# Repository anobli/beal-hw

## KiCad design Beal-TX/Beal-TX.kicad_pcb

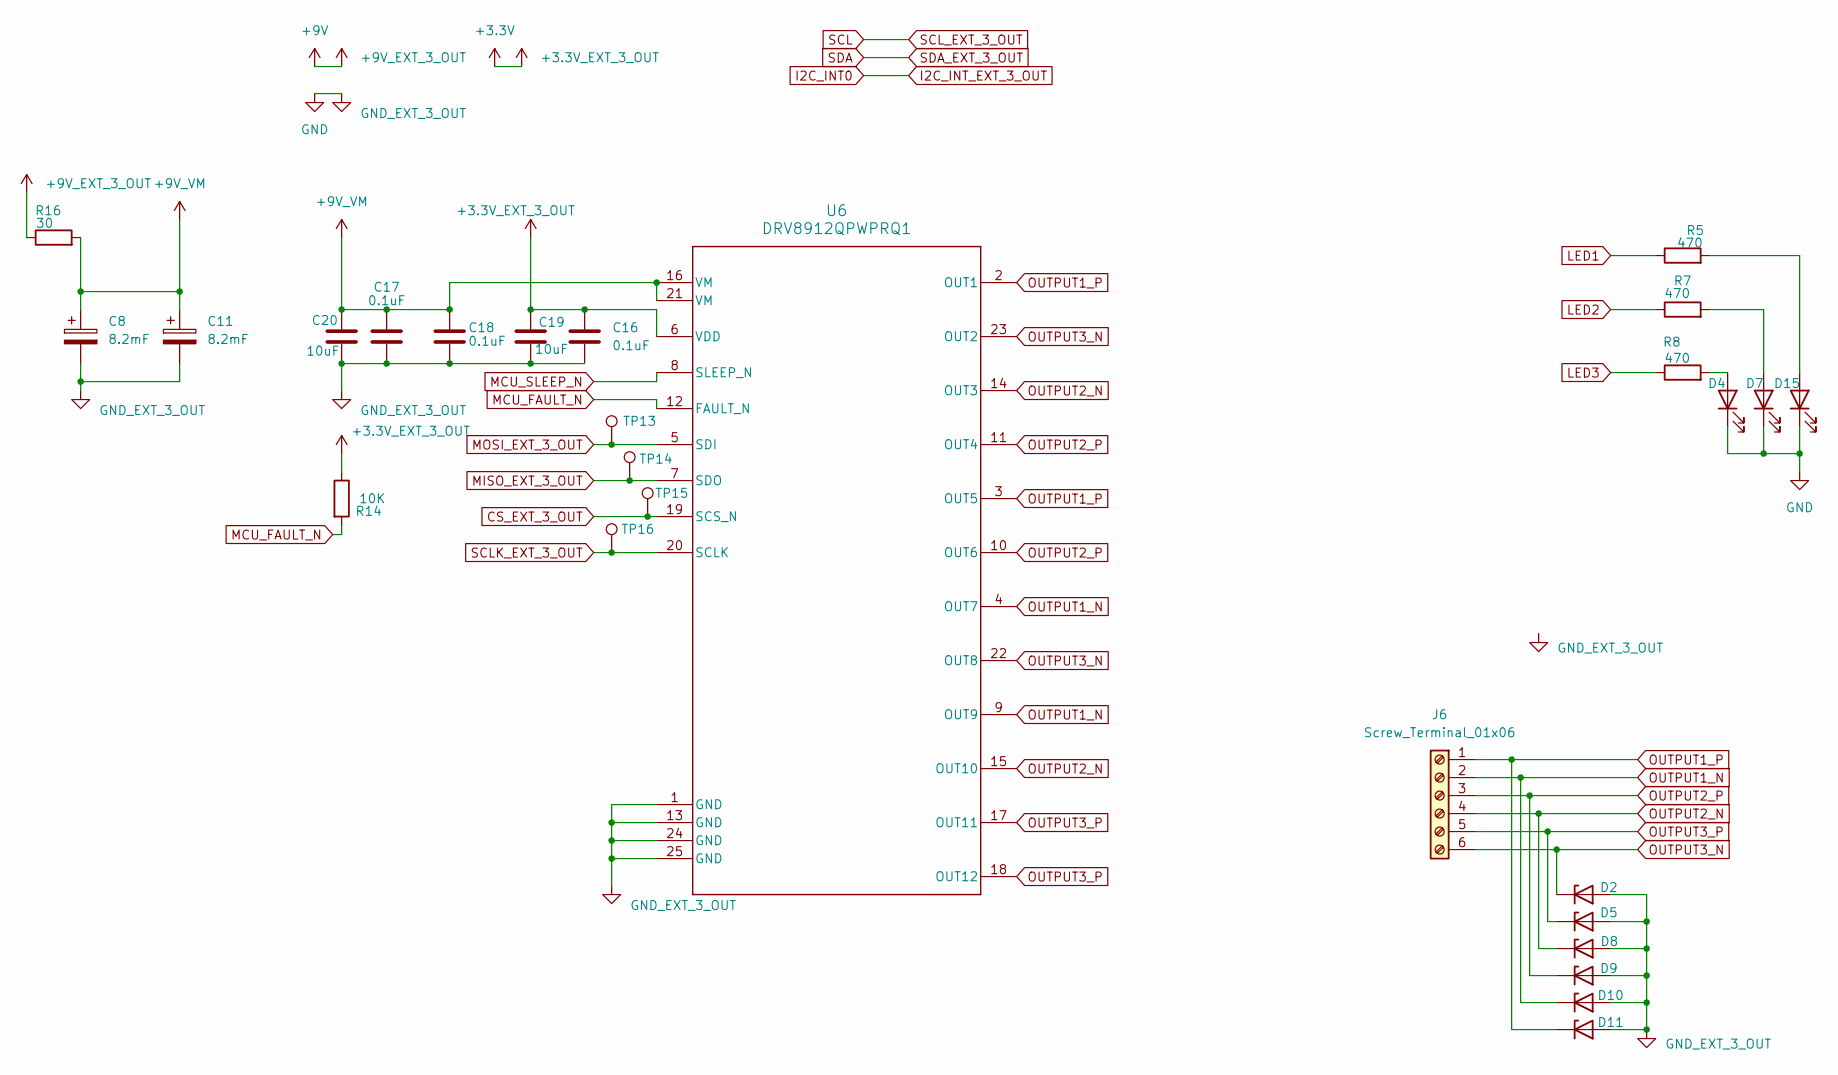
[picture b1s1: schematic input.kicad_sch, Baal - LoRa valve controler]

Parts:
C8, C11: 8.2mF; CP_Radial_D25.0mm_P10.00mm_SnapIn; MPN 8.2mF 35V
C16: 0.1uF; C_0402_1005Metric; Manufacturer_Part_Number 0,1uF 16V 0402
C17, C18: 0.1uF; C_0805_2012Metric; Manufacturer_Part_Number 0,1uF 50V 0805
C19: 10uF; C_0805_2012Metric; MPN 10uF 10V 0805
C20: 10uF; C_1206_3216Metric; MPN GRM31CR71C106KAC7L
D2, D5, D8, D9, D10, D11: ESD9X12ST5G; D_SOD-923; MPN SZESD9X12ST5G
D4, D7, D15: LED; LED_0603_1608Metric; Manufacturer_Part_Number led red 1206
J6: Screw_Terminal_01x06; 691401710006B; MPN 691401710006B
R5, R7, R8: 470; R_0402_1005Metric; MPN 470 0402
R14: 10K; R_0402_1005Metric; MPN 10K 0402
R16: 30; R_2512_6332Metric; MPN 30R 1% 2512 3W
TP13, TP14, TP15, TP16: TestPoint; TestPoint_Pad_D1.0mm
U6: DRV8912QPWPRQ1; HTSSOP-24-1EP_4.4x7.8mm_P0.65mm_EP3.4x7.8mm_Mask2.4x4.68mm_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; Manufacturer_Part_Number DRV8912QPWPRQ1

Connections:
+3.3V: C16.1, C19.1, R14.1, U6.6 (VDD); also elsewhere on the board
+9V: R16.1; also elsewhere on the board
+9V_VM: C8.1, C11.1, C17.1, C18.1, C20.1, R16.2, U6.16 (VM), U6.21 (VM)
CS_EXT_3_OUT: TP15.1 (1_1), U6.19 (SCS_N); also elsewhere on the board
GND: C8.2, C11.2, C16.2, C17.2, C18.2, C19.2, C20.2, D2.2 (A), D4.1 (K), D5.2 (A), D7.1 (K), D8.2 (A), D9.2 (A), D10.2 (A), D11.2 (A), D15.1 (K), U6.1 (GND), U6.13 (GND), U6.24 (GND), U6.25 (GND); also elsewhere on the board
LED1: R5.1; also elsewhere on the board
LED2: R7.1; also elsewhere on the board
LED3: R8.1; also elsewhere on the board
MCU_FAULT_N: R14.2, U6.12 (FAULT_N); also elsewhere on the board
MCU_SLEEP_N: U6.8 (SLEEP_N); also elsewhere on the board
MISO_EXT_3_OUT: TP14.1 (1_1), U6.7 (SDO); also elsewhere on the board
MOSI_EXT_3_OUT: TP13.1 (1_1), U6.5 (SDI); also elsewhere on the board
unnamed: D4.2 (A), R8.2
unnamed: D7.2 (A), R7.2
unnamed: D15.2 (A), R5.2
OUTPUT1_N: D10.1 (K), J6.2, U6.4 (OUT7), U6.9 (OUT9)
OUTPUT1_P: D11.1 (K), J6.1, U6.2 (OUT1), U6.3 (OUT5)
OUTPUT2_N: D8.1 (K), J6.4, U6.14 (OUT3), U6.15 (OUT10)
OUTPUT2_P: D9.1 (K), J6.3, U6.10 (OUT6), U6.11 (OUT4)
OUTPUT3_N: D2.1 (K), J6.6, U6.22 (OUT8), U6.23 (OUT2)
OUTPUT3_P: D5.1 (K), J6.5, U6.17 (OUT11), U6.18 (OUT12)
SCLK_EXT_3_OUT: TP16.1 (1_1), U6.20 (SCLK); also elsewhere on the board

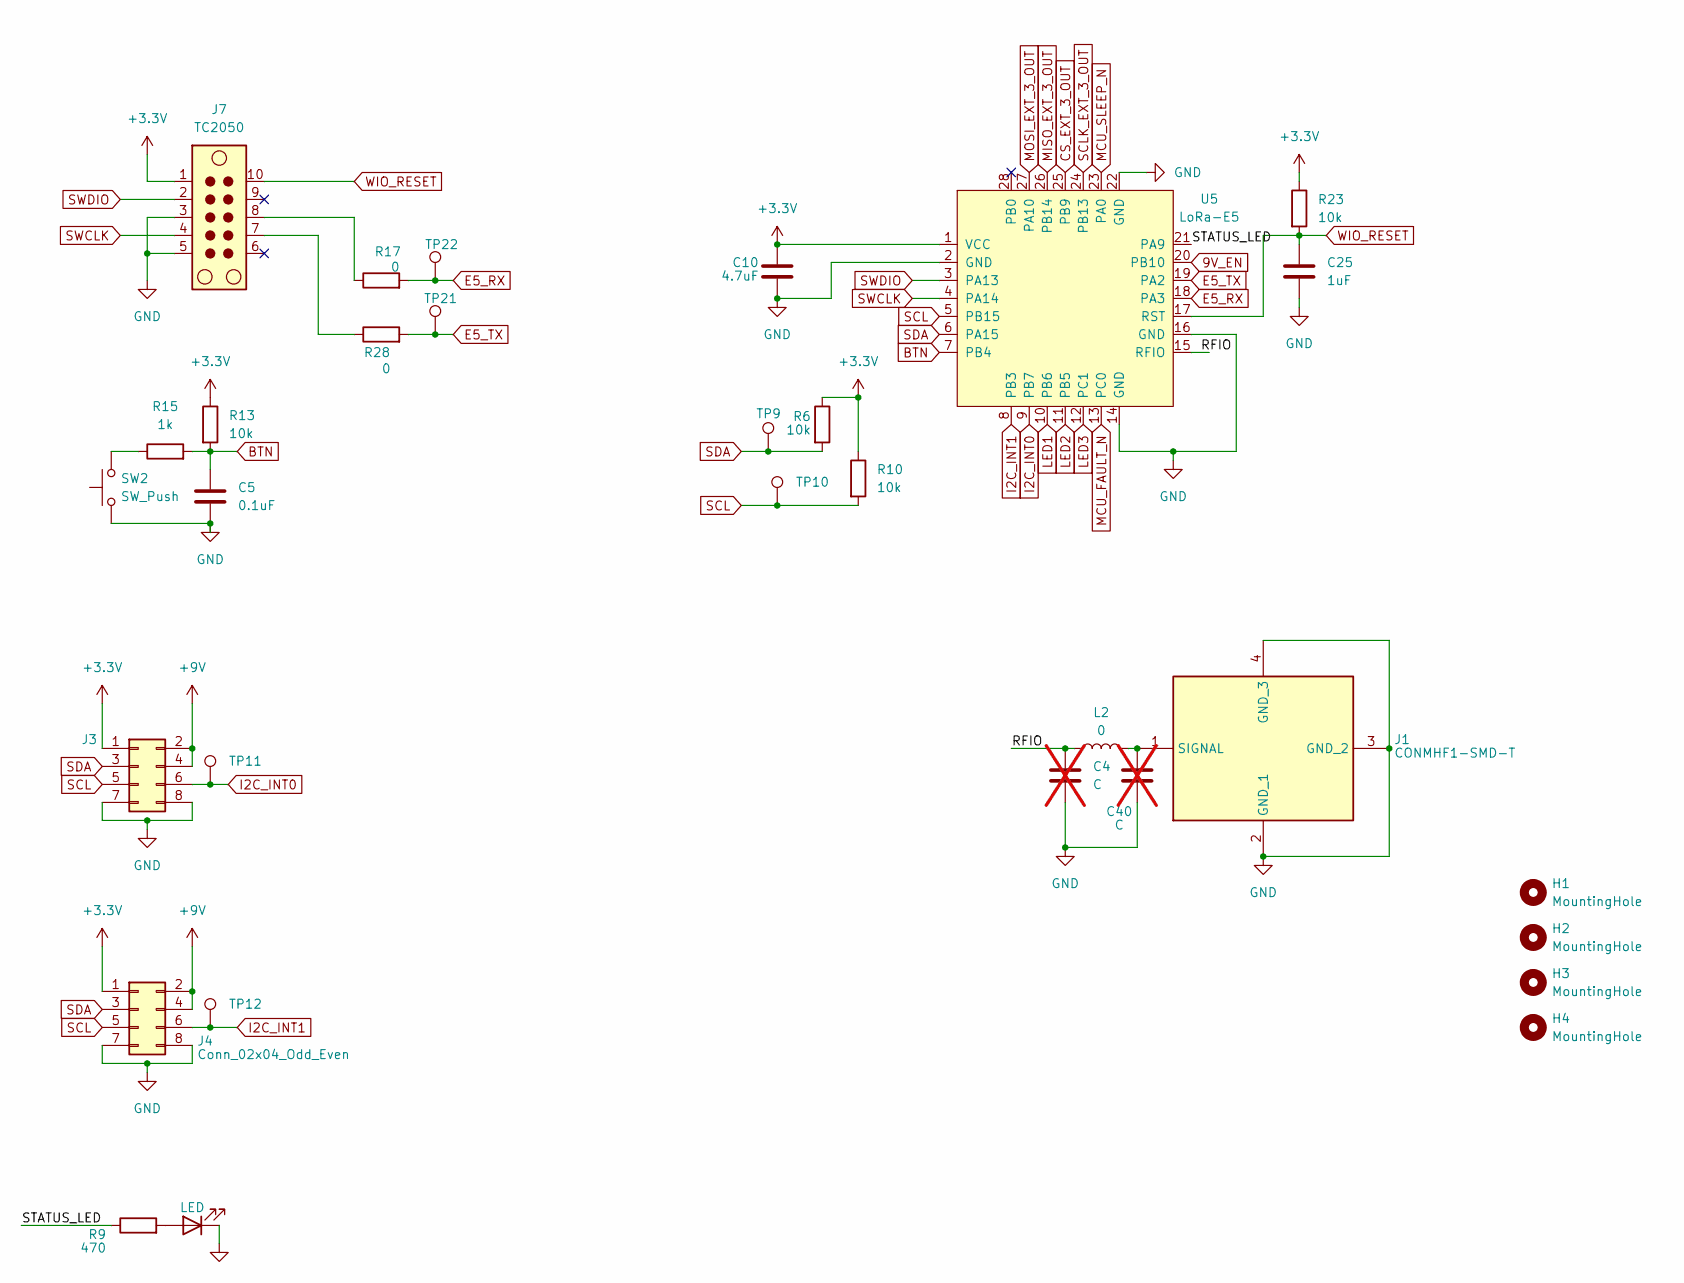
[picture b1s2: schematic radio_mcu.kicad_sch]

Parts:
C4, C40: C; C_0603_1608Metric; not fitted
C5: 0.1uF; C_0805_2012Metric; MPN 0.1uF 16V 0805
C10: 4.7uF; C_0805_2012Metric; MPN 4.7uF 10V 0805
C25: 1uF; C_0603_1608Metric; Manufacturer_Part_Number 1uF 16V 0603
D3: LED; LED_0603_1608Metric; Manufacturer_Part_Number led red 1206
H1, H2, H3, H4: MountingHole; MountingHole_2.1mm
J1: CONMHF1-SMD-T; CONMHF1SMDT; Mouser Part Number 712-CONMHF1-SMD-T
J3, J4: Conn_02x04_Odd_Even; PinHeader_2x04_P1.00mm_Vertical_SMD
J7: TC2050; Tag-Connect_TC2050-IDC-NL_2x05_P1.27mm_Vertical
L2: 0; L_0603_1608Metric; MPN 0201WMF0000TEE
R6, R10: 10k; R_0402_1005Metric; MPN 10k 0402
R9: 470; R_0402_1005Metric; MPN 470 0402
R13: 10k; R_0402_1005Metric; MPN 10K 0402
R15: 1k; R_0402_1005Metric; MPN 1k 0402
R17, R28: 0; R_0402_1005Metric; MPN 0 0402
R23: 10k; R_0402_1005Metric; Manufacturer_Part_Number 10K 0402
SW2: SW_Push; SW_PUSH_6mm; MPN TS02-66-43-BK-160-LCR-D
TP9, TP10, TP11, TP12, TP21, TP22: TestPoint; TestPoint_Pad_D1.0mm
U5: LoRa-E5; MPN LORA-E5 LORAWAN MODULE

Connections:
9V_EN: U5.20 (PB10); also elsewhere on the board
+3.3V: C10.1, J3.1, J4.1, J7.1, R6.1, R10.1, R13.1, R23.1, U5.1 (VCC); also elsewhere on the board
+9V: J3.2, J3.4, J4.2, J4.4; also elsewhere on the board
/Radio_MCU/RFIO: C4.1, L2.1, U5.15 (RFIO)
/Radio_MCU/STATUS_LED: R9.1, U5.21 (PA9)
BTN: C5.1, R13.2, R15.2, U5.7 (PB4)
CS_EXT_3_OUT: U5.25 (PB9); also elsewhere on the board
E5_RX: R17.2, TP22.1 (1_1), U5.18 (PA3)
E5_TX: R28.2, TP21.1 (1_1), U5.19 (PA2)
GND: C4.2, C5.2, C10.2, C25.2, C40.2, D3.1 (K), J1.2 (GND_1), J1.3 (GND_2), J1.4 (GND_3), J3.7, J3.8, J4.7, J4.8, J7.3, J7.5, SW2.1, U5.2 (GND), U5.14 (GND), U5.16 (GND), U5.22 (GND); also elsewhere on the board
I2C_INT0: J3.6, TP11.1 (1_1), U5.9 (PB7)
I2C_INT1: J4.6, TP12.1 (1_1), U5.8 (PB3)
LED1: U5.10 (PB6); also elsewhere on the board
LED2: U5.11 (PB5); also elsewhere on the board
LED3: U5.12 (PC1); also elsewhere on the board
MCU_FAULT_N: U5.13 (PC0); also elsewhere on the board
MCU_SLEEP_N: U5.23 (PA0); also elsewhere on the board
MISO_EXT_3_OUT: U5.26 (PB14); also elsewhere on the board
MOSI_EXT_3_OUT: U5.27 (PA10); also elsewhere on the board
unnamed: D3.2 (A), R9.2
unnamed: C40.1, J1.1 (SIGNAL), L2.2
unnamed: J7.7, R28.1
unnamed: J7.8, R17.1
unnamed: R15.1, SW2.2
SCL: J3.5, J4.5, R10.2, TP10.1 (1_1), U5.5 (PB15)
SCLK_EXT_3_OUT: U5.24 (PB13~); also elsewhere on the board
SDA: J3.3, J4.3, R6.2, TP9.1 (1_1), U5.6 (PA15)
SWCLK: J7.4, U5.4 (PA14)
SWDIO: J7.2, U5.3 (PA13)
WIO_RESET: C25.1, J7.10, R23.2, U5.17 (RST)

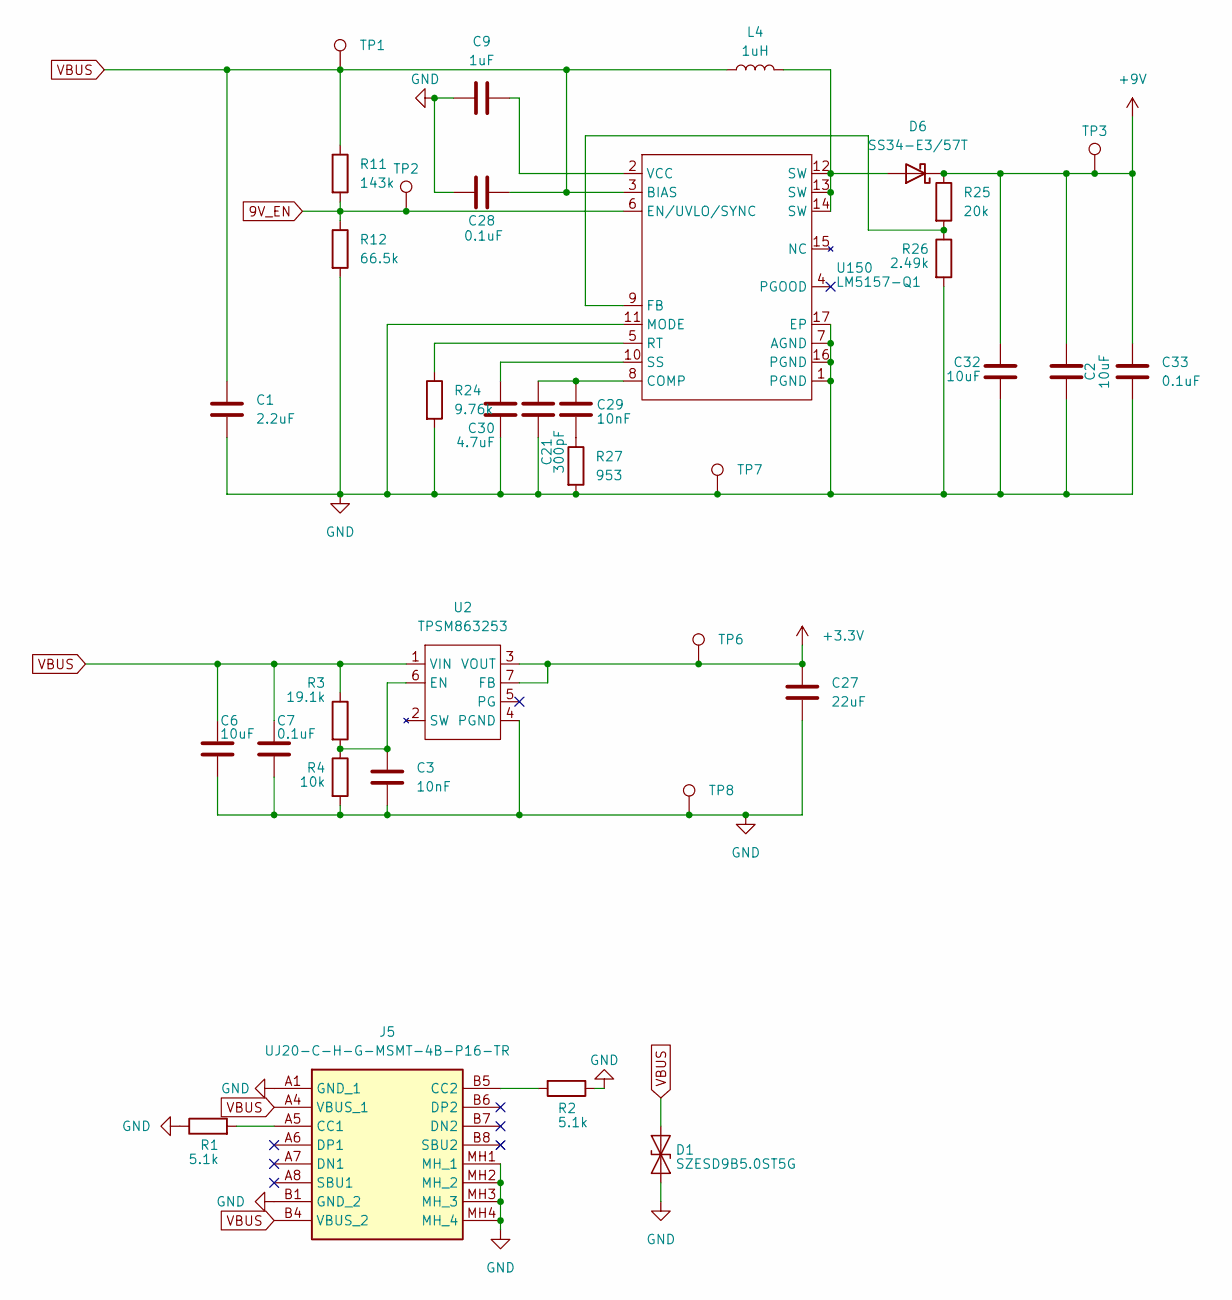
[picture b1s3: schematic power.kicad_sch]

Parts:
C1: 2.2uF; C_0805_2012Metric; Manufacturer_Part_Number GRM21BR71A225KA01L
C2, C32: 10uF; C_1206_3216Metric; Manufacturer_Part_Number GRM31CR71C106KAC7L
C3: 10nF; C_0402_1005Metric; Manufacturer_Part_Number GRM155R71C103KA01D
C6: 10uF; C_0805_2012Metric; Manufacturer_Part_Number C0805C106K8PACTU
C7: 0.1uF; C_0805_2012Metric; Manufacturer_Part_Number 08053C104KAT2A
C9: 1uF; C_0603_1608Metric; Manufacturer_Part_Number EMK107B7105KA-T
C21: 300pF; C_0402_1005Metric; Manufacturer_Part_Number GRM1555C1E301JA01D
C27: 22uF; C_0805_2012Metric; Manufacturer_Part_Number MSASL219LB5226MTNA01
C28: 0.1uF; C_0402_1005Metric; Manufacturer_Part_Number GRM155R71A104KA01D
C29: 10nF; C_0402_1005Metric; Manufacturer_Part_Number GRM155R70J103KA01D
C30: 4.7uF; C_0402_1005Metric; Manufacturer_Part_Number 4.7uF 16V
C33: 0.1uF; C_0805_2012Metric; Manufacturer_Part_Number GRM155R71C104KA88D
D1: SZESD9B5.0ST5G; D_SOD-923; MPN SZESD9B5.0ST5G
D6: SS34-E3/57T; D_SMB; Manufacturer_Part_Number SS34-E3/57T
J5: UJ20-C-H-G-MSMT-4B-P16-TR; UJ20CHGMSMT4BP16TR; Manufacturer_Part_Number UJ20-C-H-G-MSMT-4B-P16-TR
L4: 1uH; L_Wuerth_WE-PD-Typ-7345; Manufacturer_Part_Number 744777001
R1, R2: 5.1k; R_0402_1005Metric; Manufacturer_Part_Number 5.1K 0402
R3: 19.1k; R_0402_1005Metric; Manufacturer_Part_Number CRCW040219K1FKED
R4: 10k; R_0402_1005Metric; Manufacturer_Part_Number CRCW040210K0FKED
R11: 143k; R_0402_1005Metric; MPN 143k 0402
R12: 66.5k; R_0402_1005Metric; MPN 66.5k 0402
R24: 9.76k; R_0402_1005Metric; Manufacturer_Part_Number CRCW04029K76FKED
R25: 20k; R_0402_1005Metric; Manufacturer_Part_Number CRCW040220K0FKED
R26: 2.49k; R_0402_1005Metric; Manufacturer_Part_Number CRCW04022K49FKED
R27: 953; R_0402_1005Metric; Manufacturer_Part_Number CRCW0402953RFKED
TP1, TP2, TP3, TP6, TP7, TP8: TestPoint; TestPoint_Pad_D1.0mm
U2: TPSM863253; Texas_RDX0007A_QFN-FCMOD-7-3.3x4mm-P0.5mm_4EP; MPN TPSM863253RDXR
U150: LM5157-Q1; WQFN-16-1EP_3x3mm_P0.5mm_EP1.68x1.68mm_ThermalVias; Manufacturer_Part_Number LM5157QRTERQ1

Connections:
9V_EN: R11.2, R12.1, TP2.1 (1_1), U150.6 (EN/UVLO/SYNC); also elsewhere on the board
+3.3V: C27.1, TP6.1 (1_1), U2.3 (VOUT), U2.7 (FB); also elsewhere on the board
+9V: C2.1, C32.1, C33.1, D6.1 (K), R25.1, TP3.1 (1_1); also elsewhere on the board
GND: C1.2, C2.2, C3.2, C6.2, C7.2, C9.2, C21.2, C27.2, C28.1, C30.2, C32.2, C33.2, D1.1 (A1), J5.A1 (GND_1), J5.B1 (GND_2), J5.MH1 (MH_1), J5.MH2 (MH_2), J5.MH3 (MH_3), J5.MH4 (MH_4), R1.1, R2.1, R4.2, R12.2, R24.2, R26.2, R27.2, TP7.1 (1_1), TP8.1 (1_1), U2.4 (PGND), U150.1 (PGND), U150.7 (AGND), U150.11 (MODE), U150.16 (PGND), U150.17 (EP); also elsewhere on the board
unnamed: C29.2, R27.1
unnamed: D6.2 (A), L4.2, U150.12 (SW), U150.13 (SW), U150.14 (SW)
unnamed: J5.A5 (CC1), R1.2
unnamed: J5.B5 (CC2), R2.2
unnamed: C3.1, R3.2, R4.1, U2.6 (EN)
unnamed: C21.1, C29.1, U150.8 (COMP)
unnamed: R25.2, R26.1, U150.9 (FB)
unnamed: R24.1, U150.5 (RT)
unnamed: C30.1, U150.10 (SS)
unnamed: C9.1, U150.2 (VCC)
VBUS: C1.1, C6.1, C7.1, C28.2, D1.2 (A2), J5.A4 (VBUS_1), J5.B4 (VBUS_2), L4.1, R3.1, R11.1, TP1.1 (1_1), U2.1 (VIN), U150.3 (BIAS)

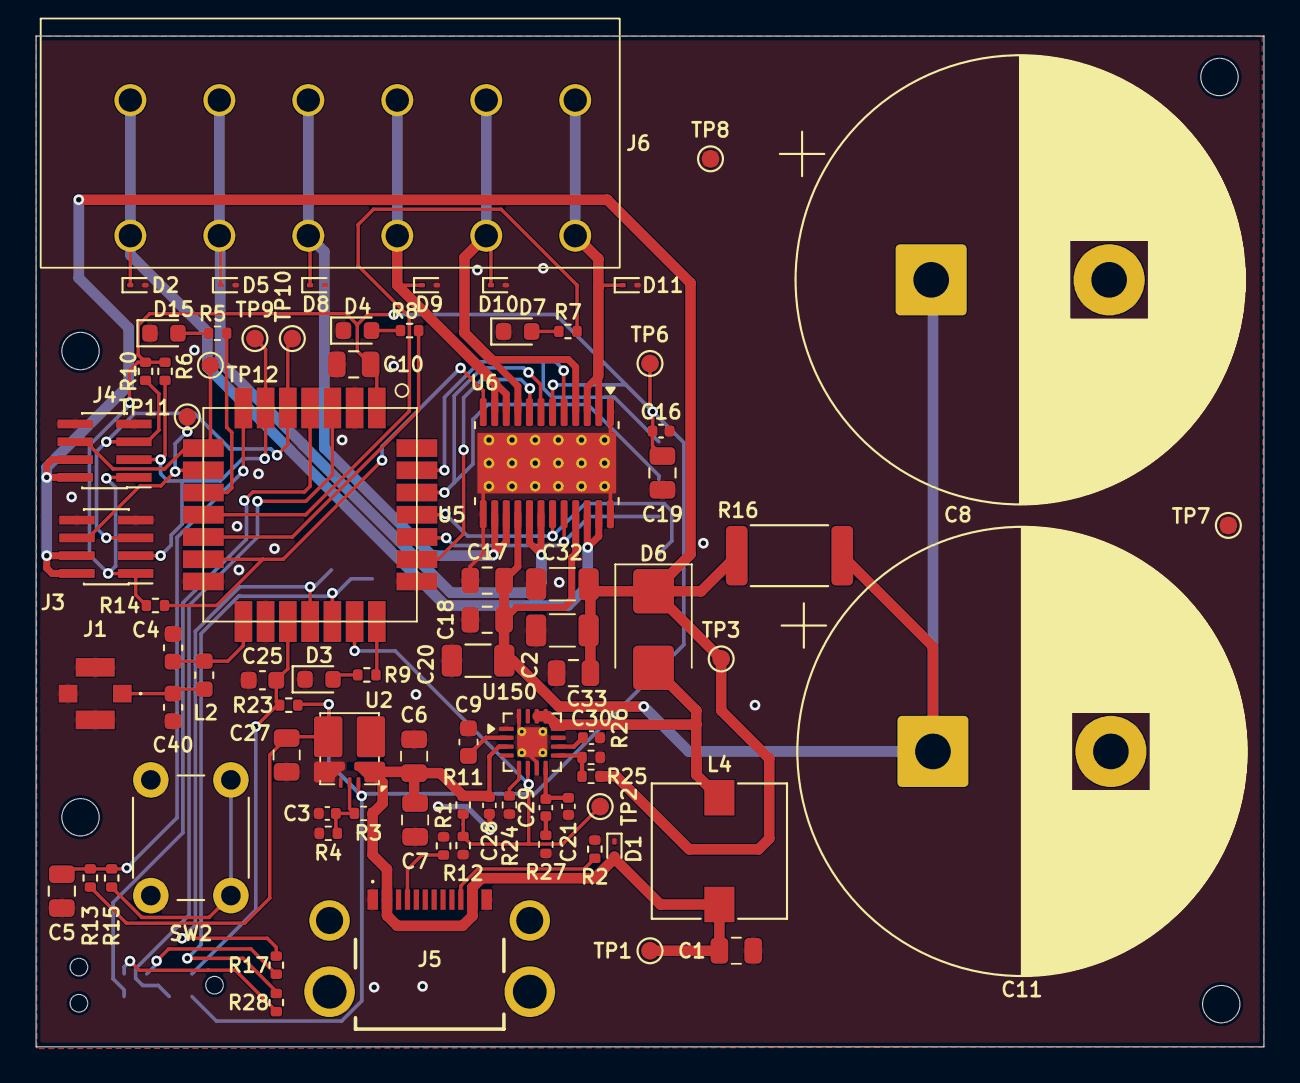
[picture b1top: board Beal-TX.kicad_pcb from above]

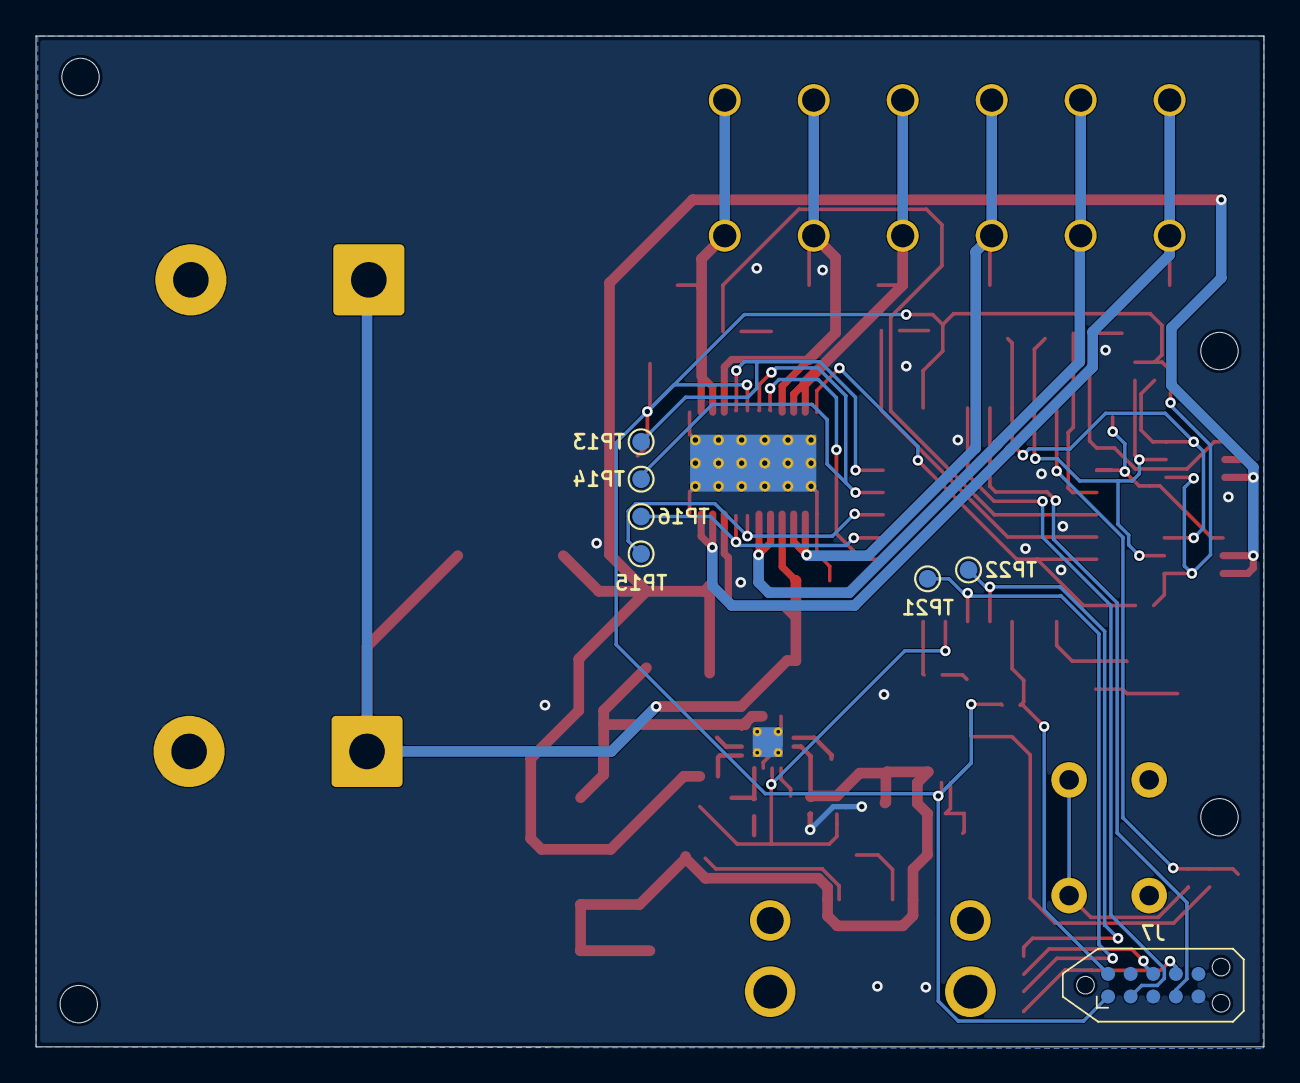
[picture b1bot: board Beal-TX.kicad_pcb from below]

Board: 2 copper layers, 69.0 x 56.8 mm, 93 parts (7 on the bottom side), 51 nets.
